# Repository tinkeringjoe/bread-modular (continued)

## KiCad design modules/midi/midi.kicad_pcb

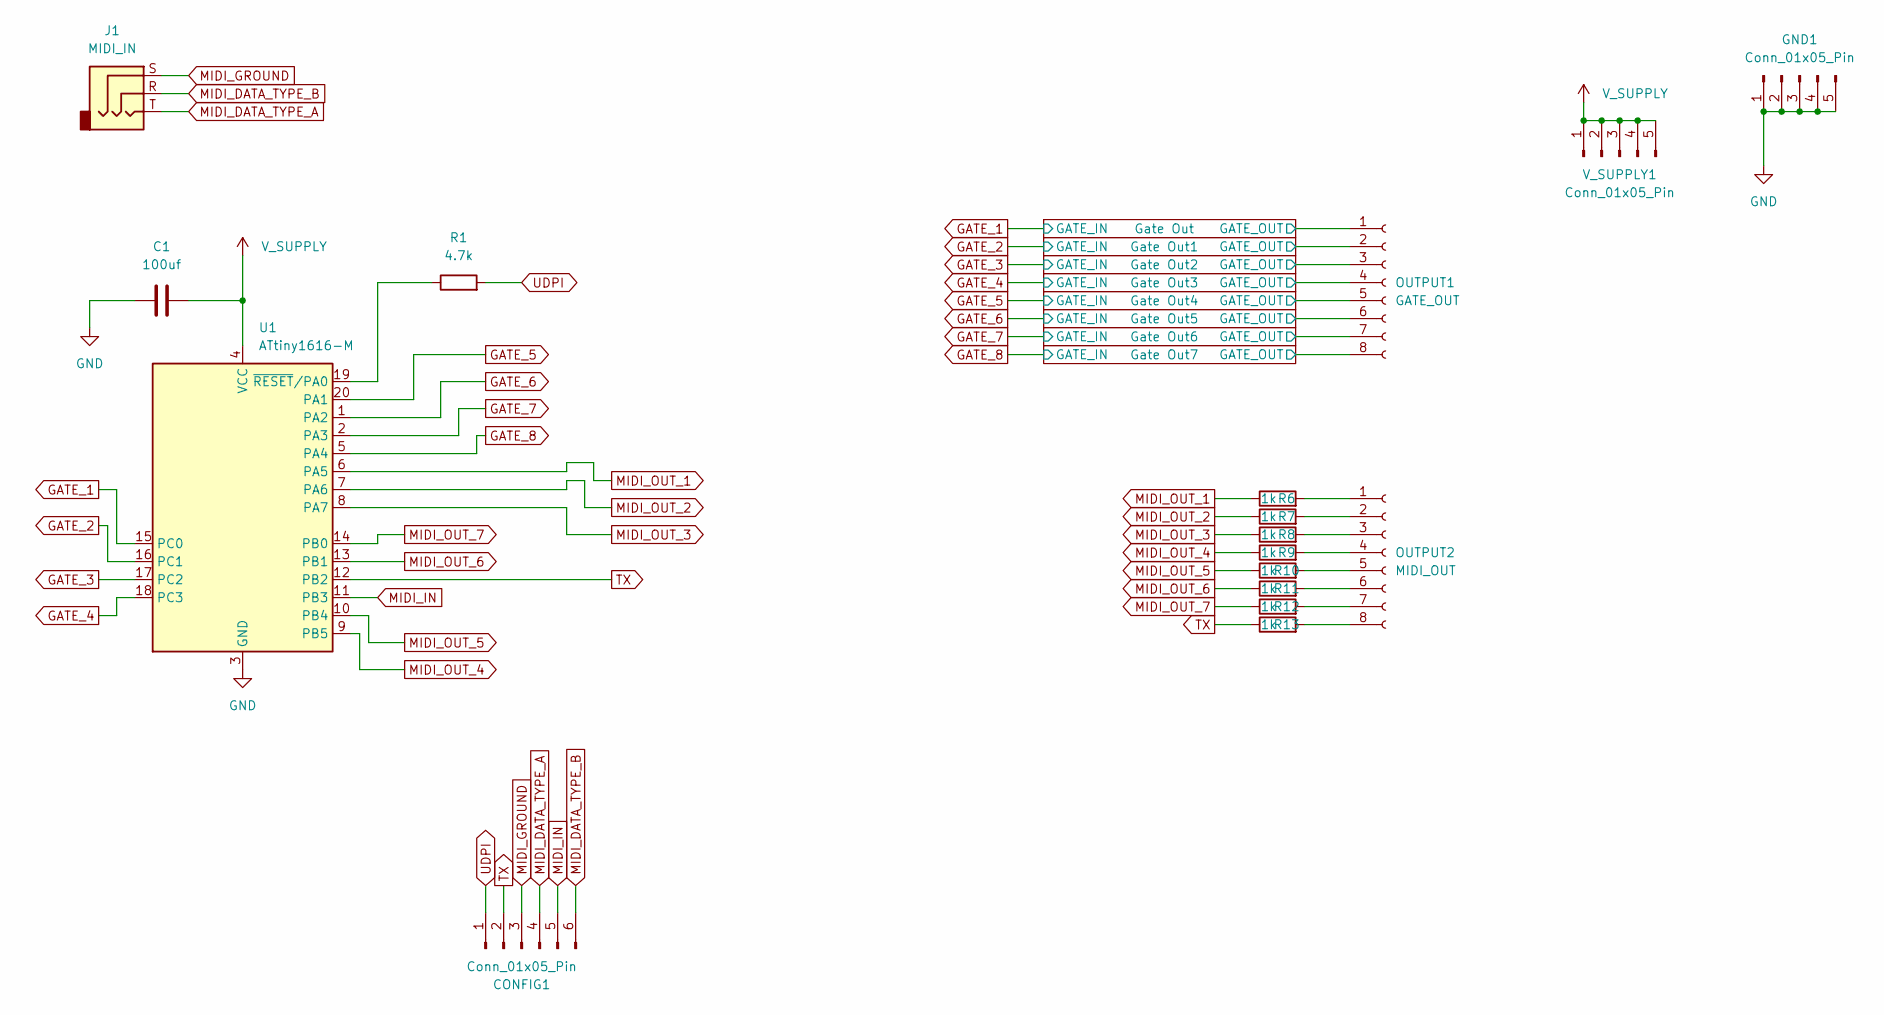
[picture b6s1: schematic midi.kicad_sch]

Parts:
C1: 100uf; C_1206_3216Metric
CONFIG1: Conn_01x05_Pin; Conn_Holes_6
GND1: Conn_01x05_Pin; Power_Connector
J1: MIDI_IN; Jack_3.5mm_QingPu_WQP-PJ366ST_Vertical
OUTPUT1: GATE_OUT; PinSocket_1x08_P2.54mm_Vertical
OUTPUT2: MIDI_OUT; PinSocket_1x08_P2.54mm_Vertical
R1: 4.7k; R_0402_1005Metric
R6, R7, R8, R9, R10, R11, R12, R13: 1k; R_0402_1005Metric
U1: ATtiny1616-M; VQFN-20-1EP_3x3mm_P0.4mm_EP1.7x1.7mm
V_SUPPLY1: Conn_01x05_Pin; Power_Connector

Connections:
/Gate Out1/GATE_OUT: OUTPUT1.2; also elsewhere on the board
/Gate Out2/GATE_OUT: OUTPUT1.3; also elsewhere on the board
/Gate Out3/GATE_OUT: OUTPUT1.4; also elsewhere on the board
/Gate Out4/GATE_OUT: OUTPUT1.5; also elsewhere on the board
/Gate Out5/GATE_OUT: OUTPUT1.6; also elsewhere on the board
/Gate Out6/GATE_OUT: OUTPUT1.7; also elsewhere on the board
/Gate Out7/GATE_OUT: OUTPUT1.8; also elsewhere on the board
/Gate Out/GATE_OUT: OUTPUT1.1; also elsewhere on the board
GATE_1: U1.15 (PC0); also elsewhere on the board
GATE_2: U1.16 (PC1); also elsewhere on the board
GATE_3: U1.17 (PC2); also elsewhere on the board
GATE_4: U1.18 (PC3); also elsewhere on the board
GATE_5: U1.20 (PA1); also elsewhere on the board
GATE_6: U1.1 (PA2); also elsewhere on the board
GATE_7: U1.2 (PA3); also elsewhere on the board
GATE_8: U1.5 (PA4); also elsewhere on the board
GND: C1.1, GND1.1, GND1.2, GND1.3, GND1.4, GND1.5, U1.3 (GND), U1.21 (GND); also elsewhere on the board
MIDI_DATA_TYPE_A: CONFIG1.4, J1.T
MIDI_DATA_TYPE_B: CONFIG1.6, J1.R
MIDI_GROUND: CONFIG1.3, J1.S
MIDI_IN: CONFIG1.5, U1.11 (PB3)
MIDI_OUT_1: R6.1, U1.6 (PA5)
MIDI_OUT_2: R7.1, U1.7 (PA6)
MIDI_OUT_3: R8.1, U1.8 (PA7)
MIDI_OUT_4: R9.1, U1.9 (PB5)
MIDI_OUT_5: R10.1, U1.10 (PB4)
MIDI_OUT_6: R11.1, U1.13 (PB1)
MIDI_OUT_7: R12.1, U1.14 (PB0)
unnamed: OUTPUT2.1, R6.2
unnamed: OUTPUT2.2, R7.2
unnamed: OUTPUT2.3, R8.2
unnamed: OUTPUT2.4, R9.2
unnamed: OUTPUT2.5, R10.2
unnamed: OUTPUT2.6, R11.2
unnamed: OUTPUT2.7, R12.2
unnamed: OUTPUT2.8, R13.2
unnamed: R1.1, U1.19 (~RESET/PA0)
TX: CONFIG1.2, R13.1, U1.12 (PB2)
UDPI: CONFIG1.1, R1.2
V_SUPPLY: C1.2, U1.4 (VCC), V_SUPPLY1.1, V_SUPPLY1.2, V_SUPPLY1.3, V_SUPPLY1.4, V_SUPPLY1.5; also elsewhere on the board

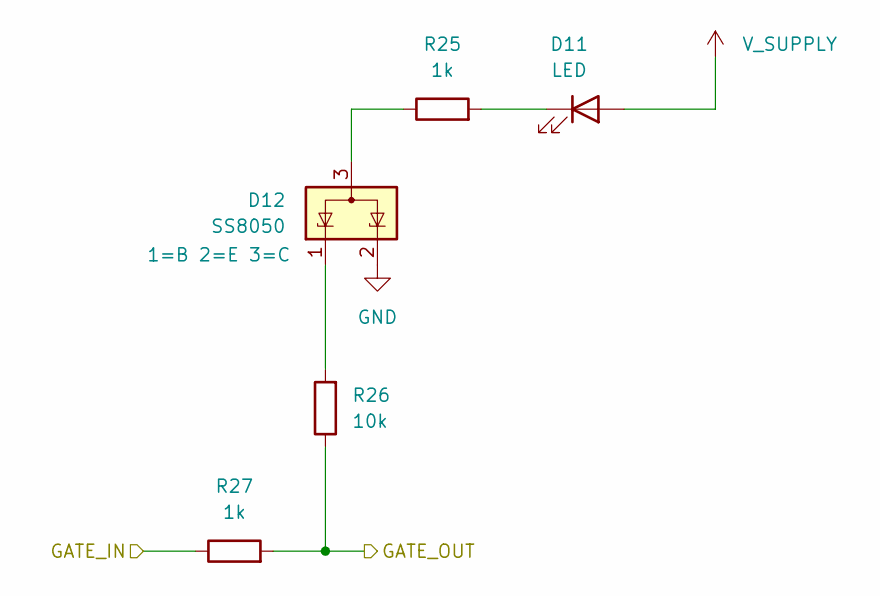
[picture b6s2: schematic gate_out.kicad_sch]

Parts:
D11: LED; LED_0603_1608Metric
D12: SS8050; SOT-23
R25, R27: 1k; R_0402_1005Metric
R26: 10k; R_0402_1005Metric

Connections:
/Gate Out5/GATE_OUT: R26.1, R27.2; also elsewhere on the board
GATE_6: R27.1; also elsewhere on the board
GND: D12.2 (K); also elsewhere on the board
unnamed: D11.1 (K), R25.2
unnamed: D12.3 (A), R25.1
unnamed: D12.1 (K), R26.2
V_SUPPLY: D11.2 (A); also elsewhere on the board

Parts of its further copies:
D1, D4, D6, D8, D13, D15, D100: LED; LED_0603_1608Metric
D2, D3, D5, D7, D10, D14, D16: SS8050; SOT-23
R2, R4, R14, R15, R17, R19, R21, R22, R24, R28, R30, R31, R33, R44: 1k; R_0402_1005Metric
R3, R5, R16, R20, R23, R29, R32: 10k; R_0402_1005Metric

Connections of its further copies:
/Gate Out1/GATE_OUT: R3.1, R14.2; also elsewhere on the board
/Gate Out2/GATE_OUT: R16.1, R17.2; also elsewhere on the board
/Gate Out3/GATE_OUT: R20.1, R21.2; also elsewhere on the board
/Gate Out4/GATE_OUT: R23.1, R24.2; also elsewhere on the board
/Gate Out6/GATE_OUT: R29.1, R30.2; also elsewhere on the board
/Gate Out7/GATE_OUT: R32.1, R33.2; also elsewhere on the board
/Gate Out/GATE_OUT: R5.1, R44.2; also elsewhere on the board
GATE_1: R44.1; also elsewhere on the board
GATE_2: R14.1; also elsewhere on the board
GATE_3: R17.1; also elsewhere on the board
GATE_4: R21.1; also elsewhere on the board
GATE_5: R24.1; also elsewhere on the board
GATE_7: R30.1; also elsewhere on the board
GATE_8: R33.1; also elsewhere on the board
GND: D2.2 (K), D3.2 (K), D5.2 (K), D7.2 (K), D10.2 (K), D14.2 (K), D16.2 (K); also elsewhere on the board
unnamed: D1.1 (K), R2.2
unnamed: D2.3 (A), R4.1
unnamed: D2.1 (K), R5.2
unnamed: D3.3 (A), R2.1
unnamed: D3.1 (K), R3.2
unnamed: D4.1 (K), R15.2
unnamed: D5.3 (A), R15.1
unnamed: D5.1 (K), R16.2
unnamed: D6.1 (K), R19.2
unnamed: D7.3 (A), R19.1
unnamed: D7.1 (K), R20.2
unnamed: D8.1 (K), R22.2
unnamed: D10.3 (A), R22.1
unnamed: D10.1 (K), R23.2
unnamed: D13.1 (K), R28.2
unnamed: D14.3 (A), R28.1
unnamed: D14.1 (K), R29.2
unnamed: D15.1 (K), R31.2
unnamed: D16.3 (A), R31.1
unnamed: D16.1 (K), R32.2
unnamed: D100.1 (K), R4.2
V_SUPPLY: D1.2 (A), D4.2 (A), D6.2 (A), D8.2 (A), D13.2 (A), D15.2 (A), D100.2 (A); also elsewhere on the board

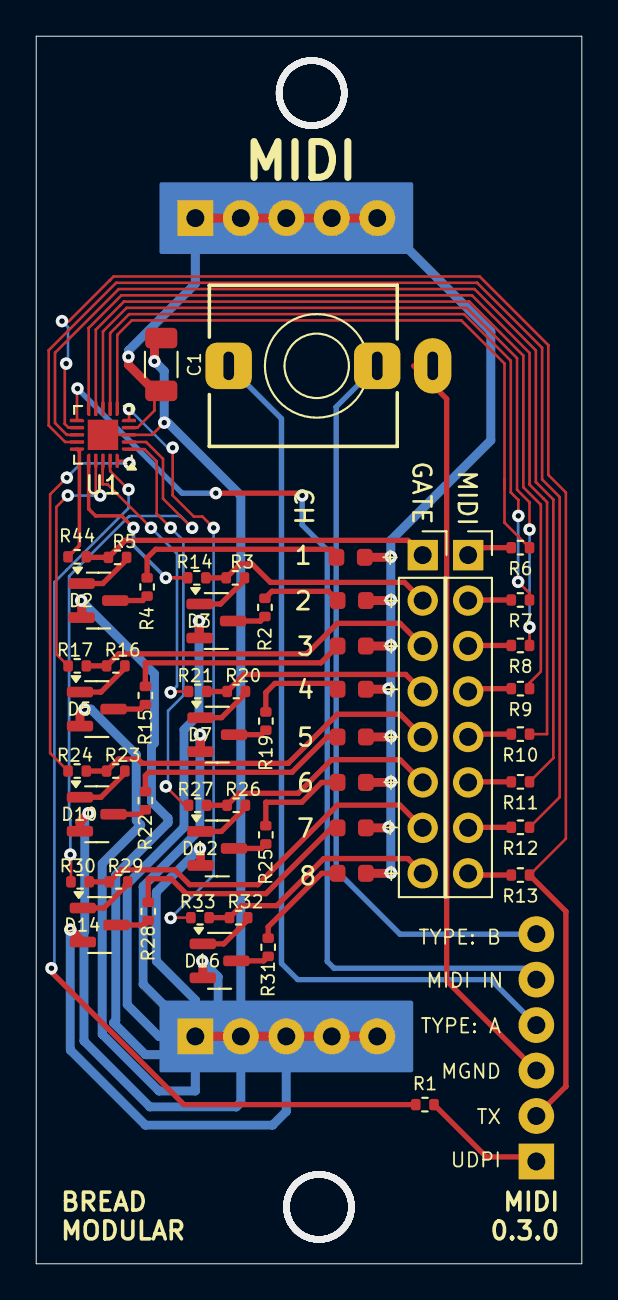
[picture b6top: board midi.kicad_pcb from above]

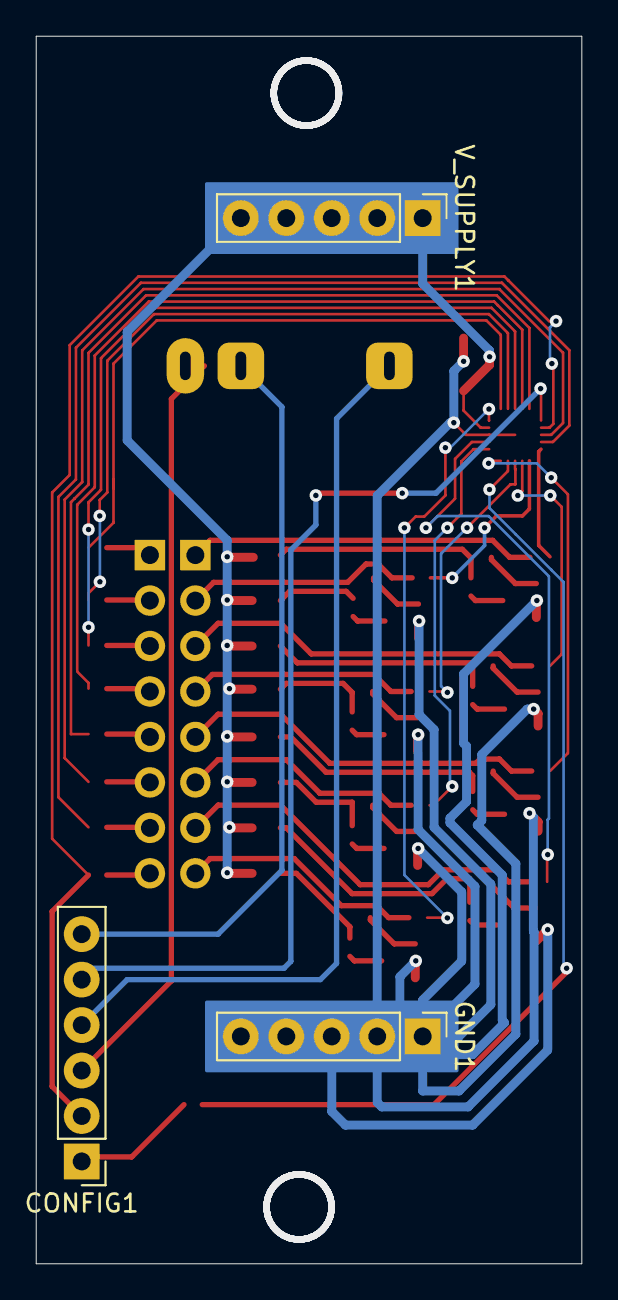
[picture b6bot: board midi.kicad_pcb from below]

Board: 2 copper layers, 30.5 x 68.6 mm, 57 parts (3 on the bottom side), 64 nets.

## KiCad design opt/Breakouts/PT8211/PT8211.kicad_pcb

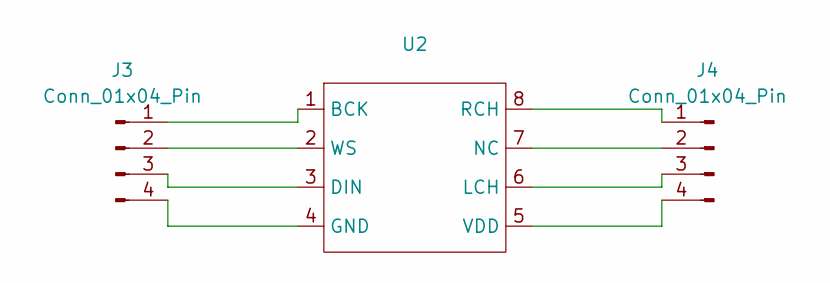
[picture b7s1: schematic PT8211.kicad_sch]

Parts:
J3, J4: Conn_01x04_Pin; PinSocket_1x04_P2.54mm_Vertical
U2: SOIC-8-1EP_3.9x4.9mm_P1.27mm_EP2.29x3mm

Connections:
unnamed: J3.1, U2.1 (BCK)
unnamed: J3.2, U2.2 (WS)
unnamed: J3.3, U2.3 (DIN)
unnamed: J3.4, U2.4 (GND)
unnamed: J4.1, U2.8 (RCH)
unnamed: J4.2, U2.7 (NC)
unnamed: J4.3, U2.6 (LCH)
unnamed: J4.4, U2.5 (VDD)

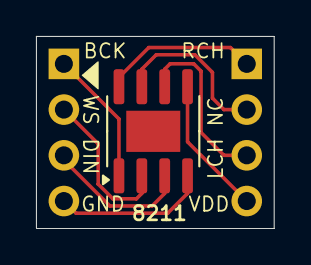
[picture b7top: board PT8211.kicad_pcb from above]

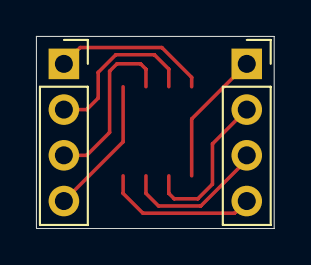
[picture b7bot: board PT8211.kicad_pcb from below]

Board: 2 copper layers, 13.2 x 10.7 mm, 3 parts (2 on the bottom side), 8 nets.

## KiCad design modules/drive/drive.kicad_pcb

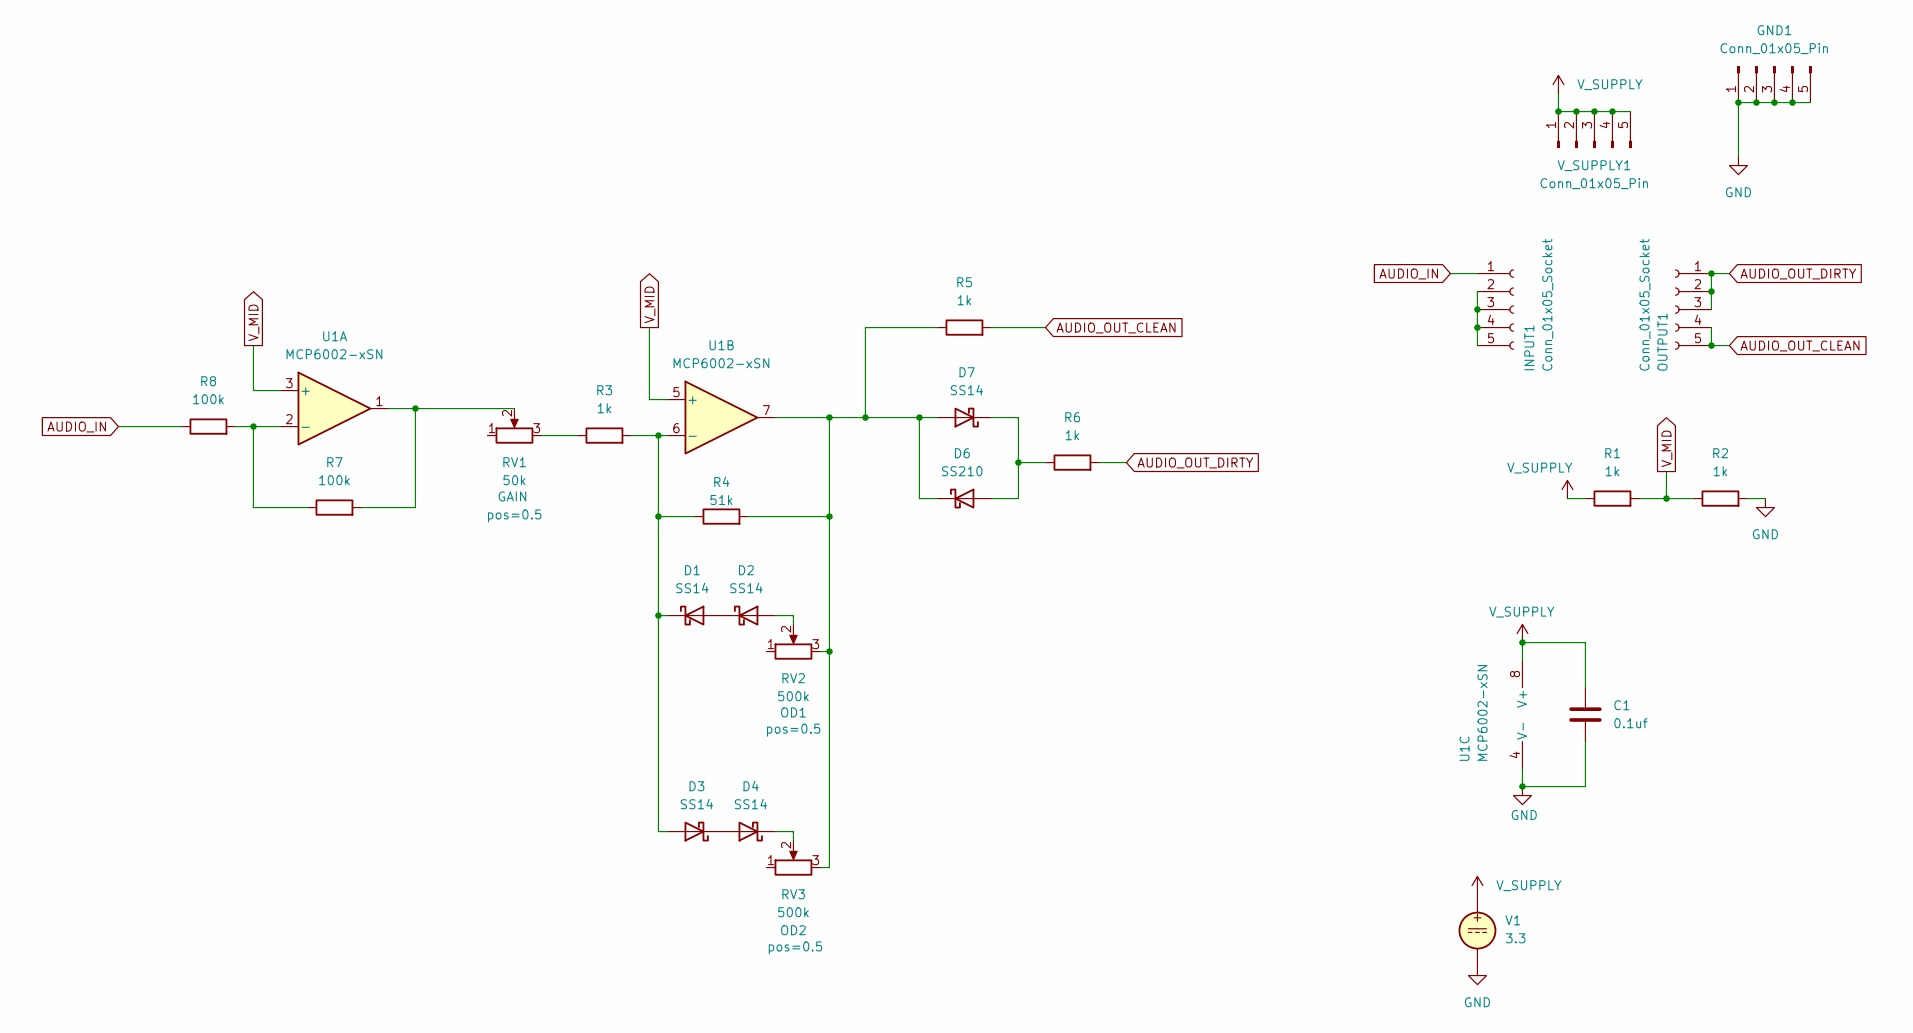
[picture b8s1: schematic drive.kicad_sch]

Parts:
C1: 0.1uf; C_0402_1005Metric
D1, D2, D3, D4, D7: SS14; D_SMA
D6: SS210; D_SMA
GND1: Conn_01x05_Pin; Power_Connector
INPUT1: Conn_01x05_Socket; PinSocket_1x05_P2.54mm_Vertical
OUTPUT1: Conn_01x05_Socket; PinSocket_1x05_P2.54mm_Vertical
R1, R2, R3, R5, R6: 1k; R_0402_1005Metric
R4: 51k; R_0402_1005Metric
R7, R8: 100k; R_0402_1005Metric
RV1: 50k; Potentiometer_RV09
RV2, RV3: 500k; Potentiometer_RV09
U1: MCP6002-xSN; SOIC-8-1EP_3.9x4.9mm_P1.27mm_EP2.29x3mm
V1: 3.3
V_SUPPLY1: Conn_01x05_Pin; Power_Connector

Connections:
AUDIO_IN: INPUT1.1, R8.1
AUDIO_OUT_CLEAN: OUTPUT1.4, OUTPUT1.5, R5.2
AUDIO_OUT_DIRTY: OUTPUT1.1, OUTPUT1.2, OUTPUT1.3, R6.2
GND: C1.2, GND1.1, GND1.2, GND1.3, GND1.4, GND1.5, R2.2, U1.4 (V-), V1.2
unnamed: D1.2 (A), D2.1 (K)
unnamed: D1.1 (K), D3.2 (A), R3.2, R4.1, U1.6 (-)
unnamed: D2.2 (A), RV2.2
unnamed: D3.1 (K), D4.2 (A)
unnamed: D4.1 (K), RV3.2
unnamed: D6.2 (A), D7.1 (K), R6.1
unnamed: D6.1 (K), D7.2 (A), R4.2, R5.1, RV2.3, RV3.3, U1.7
unnamed: INPUT1.2, INPUT1.3, INPUT1.4, INPUT1.5
unnamed: R3.1, RV1.3
unnamed: R7.2, RV1.2, U1.1
unnamed: R7.1, R8.2, U1.2 (-)
V_MID: R1.2, R2.1, U1.3 (+), U1.5 (+)
V_SUPPLY: C1.1, R1.1, U1.8 (V+), V1.1, V_SUPPLY1.1, V_SUPPLY1.2, V_SUPPLY1.3, V_SUPPLY1.4, V_SUPPLY1.5

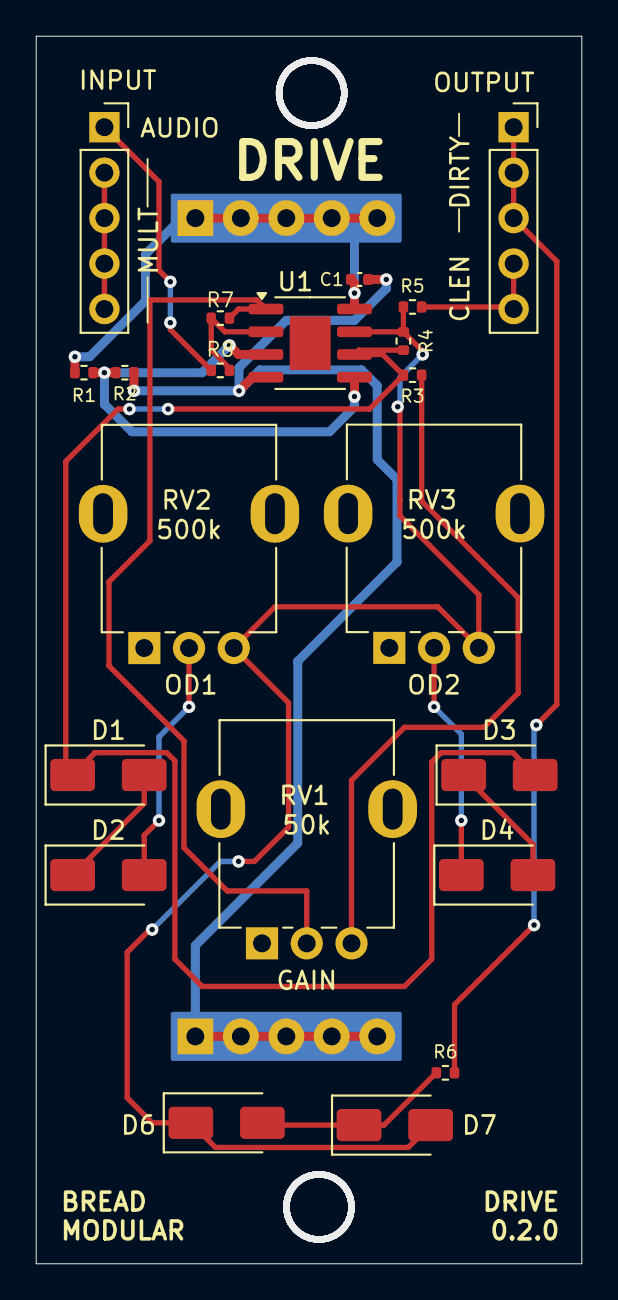
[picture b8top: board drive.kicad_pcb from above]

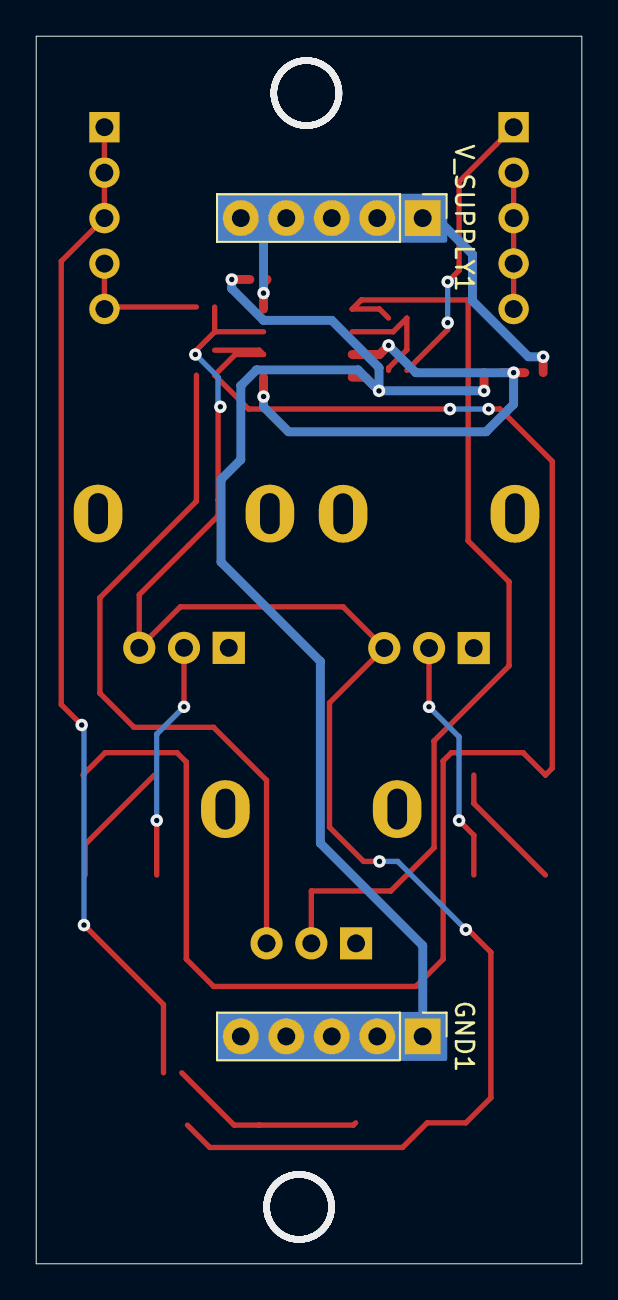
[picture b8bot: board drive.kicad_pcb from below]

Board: 2 copper layers, 30.5 x 68.6 mm, 23 parts (2 on the bottom side), 17 nets.

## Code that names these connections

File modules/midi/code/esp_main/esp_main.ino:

/* Arduino ATTiny 1616 Pin Map

  0 - PA4
  1 - PA5
  2 - PA6
  3 - PA7
  4 - PB5
  5 - PB4
  6 - PB3, RX
  7 - PB2, TX
  8 - PB1
  9 - PB0
  10 - PC0
  11 - PC1
  12 - PC2
  13 - PC3
  14 - PA1
  15 - PA2
  16 - PA3
*/

#include <MIDI.h>
#include <SoftwareSerial.h>

// Create a MIDI object
MIDI_CREATE_INSTANCE(HardwareSerial, Serial, MIDI);

#define PIN_RX 6 // PB3
#define PIN_TX 7 // PB2

// Define the Gate Pins
#define GATE_PIN_01 10 // PC0
#define GATE_PIN_02 11 // PC1
#define GATE_PIN_03 12 // PC2
#define GATE_PIN_04 13 // PC3
#define GATE_PIN_05 14 // PA1
#define GATE_PIN_06 15 // PA2
#define GATE_PIN_07 16 // PA3
#define GATE_PIN_08 0 // PA4

// Define IMIDI Pins
#define IMIDI_PIN_01 1 // PA5
#define IMIDI_PIN_02 2 // PA6
#define IMIDI_PIN_03 3 // PA7
#define IMIDI_PIN_04 4 // PB5
#define IMIDI_PIN_05 5 // PB4
#define IMIDI_PIN_06 8 // PB1
#define IMIDI_PIN_07 9 // PB0

SoftwareSerial midiSerialArray[] = {
    SoftwareSerial(-1, IMIDI_PIN_01),
    SoftwareSerial(-1, IMIDI_PIN_02),
    SoftwareSerial(-1, IMIDI_PIN_03),
    SoftwareSerial(-1, IMIDI_PIN_04),
    SoftwareSerial(-1, IMIDI_PIN_05),
    SoftwareSerial(-1, IMIDI_PIN_06),
    SoftwareSerial(-1, IMIDI_PIN_07),
};

int getGatePin(int id) {
  switch (id) {
    case 1:
      return GATE_PIN_01;
    case 2:
      return GATE_PIN_02;
    case 3:
      return GATE_PIN_03;
    case 4:
      return GATE_PIN_04;
    case 5:
      return GATE_PIN_05;
    case 6:
      return GATE_PIN_06;
    case 7:
      return GATE_PIN_07;
    case 8:
      return GATE_PIN_08;
    default:
      return -1;
  }
}

void setupGates() {
  for (int x = 1; x <= 8; x = x + 1) {
    int gatePin = getGatePin(x);
    pinMode(gatePin, OUTPUT);
    digitalWrite(gatePin, LOW);
  }
}

void setupIMIDI() {
  pinMode(IMIDI_PIN_01, OUTPUT);
  pinMode(IMIDI_PIN_02, OUTPUT);
  pinMode(IMIDI_PIN_03, OUTPUT);
  pinMode(IMIDI_PIN_04, OUTPUT);
  pinMode(IMIDI_PIN_05, OUTPUT);
  pinMode(IMIDI_PIN_06, OUTPUT);
  pinMode(IMIDI_PIN_07, OUTPUT);

  for (int i = 0; i < 7; i++) {
    midiSerialArray[i].begin(31250); // Start each SoftwareSerial at MIDI baud rate
  }
}

void handleNoteOn(byte channel, byte note, byte velocity) {
  int gatePin = getGatePin(channel);
  if (gatePin != -1) {
    digitalWrite(gatePin, HIGH);
  }
  
  sendMIDI(channel, 0x90, note, velocity);
}

// Callback for Note Off messages
void handleNoteOff(byte channel, byte note, byte velocity) {
  int gatePin = getGatePin(channel);
  if (gatePin != -1) {
    digitalWrite(gatePin, LOW);
  }

  sendMIDI(channel, 0x80, note, velocity);
}

void sendMIDI(byte channel, byte status, byte data1, byte data2) {
  int channelIndex = channel - 1;
  if (channelIndex >= 0 && channelIndex < 7) {
    SoftwareSerial serialCh = midiSerialArray[channelIndex];
    serialCh.write(status); // Send the status byte
    serialCh.write(data1);  // Send the first data byte
    serialCh.write(data2);  // Send the second data byte
  }
}

void setup() {
  setupGates();

  Serial.begin(31250);
   // Initialize the MIDI library
  MIDI.begin(MIDI_CHANNEL_OMNI); // Listen to all MIDI channels
  MIDI.setHandleNoteOn(handleNoteOn);
  MIDI.setHandleNoteOff(handleNoteOff);

  setupIMIDI();

  Serial.println("MIDI Listening Started!");
}

void loop() {
  MIDI.read();
}

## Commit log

2024-10-04 Create LICENSE
2024-10-04 Add the 4_ATT module
2024-10-04 Add aa module for the buff_mix
2024-10-04 Add the final buff_mix
2024-10-07 Add line_in schematic
2024-10-07 Add the schematic for the PCB
2024-10-07 Update the line-in module
2024-10-07 Make sure SMD via are not placed on pads.
2024-10-07 version line_in_0.2.0
2024-10-14 Retouched the Blank Module with new sizes.
2024-10-14 Add the gitignore file
2024-10-14 Add basic version of 4_mix
2024-10-14 Implement the simulation model.
2024-10-15 Updated the core design
2024-10-15 Fixed some pcb layout issues.
2024-10-15 Add the full mixer
2024-10-16 Schematics is done. Now it's time for PCB layout.
2024-10-16 Add some external KiCad footprints lib.
2024-10-16 Implemented the PCB design of 4_mix
2024-10-16 Change some routing rules.
2024-10-16 Finalized 4_mix for production
2024-10-16 Add sockets for the blank project.
2024-10-17 Start working on the new version of line_in
2024-10-17 Finalize the core design
2024-10-17 Add AudioJacks submodule with KiCad footprints.
2024-10-17 Finalize the schematic design
2024-10-17 Finished building the line_in module.
2024-10-17 Add the line_in 0.3.0 production build
2024-10-18 Add the initial version of the line_out
2024-10-18 Finalized the line_out module.
2024-10-20 Build line_out for production
2024-10-20 Add BreakoutBoards for popular opamps.
2024-10-20 Finlalized schematic for head_out module.
2024-10-20 Finished pcb_design of the head_out
2024-10-20 Finialize the design based on actual wattage requirements.
2024-10-21 Finalize the head_out module.
2024-10-27 Use TL072 the current version has some pops and cracks LM358 could be the issue. So, we are trying TL072
2024-10-27 4_mix_0.2.0
2024-10-27 Use MCP6002 in the 4_mix. This provides more headroom due to it's rail-2-rail output.
2024-10-27 4_mix_0.3.0
2024-10-28 Add missing production files for 4_mix
2024-10-28 4_mix_0.3.1
2024-10-28 Update the basic kidcad app Add simulation support Introduce the version number silkscreen
2024-10-28 Setup JVCA
2024-10-28 Implement the basic setup. CV support is not done and there are no CV control implemented.
2024-10-28 Finish the jvca signal handling.
2024-10-28 Add CV controlling support
2024-10-29 Assigned footprints
2024-10-29 Implemented JVCA PCB
2024-10-29 Fix the simulation a bit.
2024-10-29 Add jvca production data
2024-10-29 jcva_0.1.0
2024-11-01 Implement the base
2024-11-01 Add the version text
2024-11-01 base_1.0.0
2024-11-01 Created a RV_09 base Now we can use these inside the breadboard along with some circuit. Or inside BBM Base.
2024-11-01 rv_base_0.1.0
2024-11-03 Update the blank module with more details.
2024-11-03 Finished the schematic
2024-11-04 Finalize the PCB
2024-11-04 ar_env_0.1.0
2024-11-04 Changed the 6.8k resistor package. Used 0603 package due to availability in JLCPCB
2024-11-04 ar_env_0.1.1
2024-11-05 Finished schematic of wave module.
2024-11-05 Finish schematics
2024-11-05 Initiate the PCB layut
2024-11-05 Finished PCB design.
2024-11-05 wave_0.1.0
2024-11-05 Add README for the wave project.
2024-11-05 Add output wave captions.
2024-11-05 wave_0.1.1
2024-11-06 Introduce a README for JVCA
2024-11-06 Add the initial version
2024-11-06 usb_power_0.1.0
2024-11-06 Changed the orientation of the USB C port
2024-11-06 usb_power_0.1.1
2024-11-06 Add usb_power Readme
2024-11-06 Update TypeC.pretty to use our own fork with changes.
2024-11-07 Change usb_power for the TypeC footprint update.
2024-11-07 usb_power_0.1.2
2024-11-08 Implement 5V DC Power setup.
2024-11-08 dc_power_0.1.0
2024-11-10 Add power/gnd jacks
2024-11-10 base_0.2.0
2024-11-10 Add 2 jack sockets for cascading support.
2024-11-10 base_0.2.1
2024-11-12 Add the schematic of low_pass filter
2024-11-12 Add Sallen Key capacitors with commonly available caps
2024-11-12 Making the schematic ready for PCB
2024-11-12 Finalized the design
2024-11-12 layout components in the PCB
2024-11-12 update pcb layout
2024-11-13 Finalized the PCB design
2024-11-13 Build production files of low_pass
2024-11-13 Finalized low_pass
2024-11-13 low_pass_0.1.0
2024-11-14 Finished the schematic for v2ca
2024-11-14 Finished the PCB layout.
2024-11-14 Add the production version.
2024-11-14 v2ca_0.1.0
2024-11-14 Add AR_ENV README.
2024-11-15 Designed the new buff_mix 0.2.0 schematic.
2024-11-15 Add the PCB layout of buff_mix
2024-11-15 Finished routing and production build
2024-11-16 buff_mix_0.2.0
2024-11-17 Add production files.
2024-11-17 usb_power_0.2.0
2024-11-17 Update line_in to use MCP6001 and 3V3.
2024-11-17 Add production line_in 0.2.0
2024-11-17 line_in_0.2.0
2024-11-17 line_in_0.4.0
2024-11-17 Update the blank module.
2024-11-18 Add the basic schematic.
2024-11-18 Add MIDI PCB
2024-11-18 Finalized the midi module.
2024-11-20 Add Attiny1616 board
2024-11-20 midi_0.1.0
2024-11-21 Finalized Kick schamatic
2024-11-22 Assign footprints and PCB ready.
2024-11-22 Finished the 4 layer board.
2024-11-22 kick_0.1.0
2024-11-23 Introduced new low_pass gate.
2024-11-24 Finalized the schematic of low_pass
2024-11-24 low_pass_0.2.0
2024-11-24 Removed the usb_power tactile switch
2024-11-24 usb_power_0.3.0
2024-11-25 Add the dummy code
2024-11-26 Implement the MIDI to Gate setup with ATTiny1616
2024-11-26 Add POC support for modular MIDI
2024-11-26 Add iMIDI support to the midi
2024-11-27 Implement the PCB layout and routing
2024-11-27 Add production files
2024-11-27 midi_0.2.0
2024-11-30 Add 1616 Tone codes.
2024-11-30 Add MIDI and gate support
2024-12-02 Add support for detuning.
2024-12-04 Send the velocity out via PA6
2024-12-05 Add schematics for the mco
2024-12-05 Finalized the PCB design of MCO
2024-12-05 Add production files for mco
2024-12-05 mco_0.1.0
2024-12-05 Convert midi codebase into platformio
2024-12-06 Removed old arduino midi codebase
2024-12-06 midi_0.2.1
2024-12-07 Add basic noise setup
2024-12-07 Implement noise tone control
2024-12-08 Implement the noise schematics
2024-12-09 Implement the PCB routing
2024-12-09 Add noise_0.1.0 production files.
2024-12-09 noise_0.1.0
2024-12-09 increased the overall delay time of the noise module code
2024-12-09 noise_0.1.1
2024-12-10 Implement the basic SVF simulation.
2024-12-11 Implement the base filter simulation
2024-12-11 Implement the final schematic for SVF
2024-12-11 Add inline documentation for the SVF
2024-12-11 Simplify the SVF design with just freq & resonance knobs
2024-12-11 Getting it ready for PCB routing
2024-12-12 Finalized the PCB routing
2024-12-12 Change the opt Kicad lib repository.
2024-12-12 svf_0.1.0
2024-12-13 Add CVMath codebase
2024-12-13 Make sure cv calculations are normalized
2024-12-14 Add a basic mode select setup
2024-12-14 Write the mode to the EEPROM
2024-12-14 Add codebase for all the modes
2024-12-14 Introduce the schematic
2024-12-14 Implement the schematic of cv_math
2024-12-15 Finished cv_math PCB routing
2024-12-15 Add cv_math production files
2024-12-15 cv_math_0.1.0
2024-12-15 Implement a basic xpand algorithm for cv_math
2024-12-15 cv_math_0.1.1
2024-12-15 cv_math: xpand now uses distance to scale this will make the waveform strech to the highest. It's bottom part won't move anywhere
2024-12-15 cv_math_0.1.2
2024-12-16 drive: Implement the schematics
2024-12-16 drive: finished pcb routing
2024-12-16 drive: add production files
2024-12-16 drive_0.1.0
2024-12-21 blank:Add opamp & pot as a built-in components These are used in almost all the projects. So, having pre-build components make is easy to get started
2024-12-21 started with the filter and VCA
2024-12-21 Implement the gate to pulse generator.
2024-12-21 Add a opamp buffer for the CV_ACCENT
2024-12-22 Finished schematics
2024-12-23 Started basic pcb layout
2024-12-23 Complete CPU routing
2024-12-23 hihat_0.1.0
2024-12-23 Add schematic for i_mix
2024-12-24 i_mix_0.1.0
2024-12-24 svf: make it louder & add curve control Now the SVF is 8db louder in general. Now the resonance control active troughout the potentiometer Add the curve support for the freq so, we can target low or 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
2024-12-24 svf_0.2.0
2024-12-24 svf: add production files for 0.2.0
2024-12-24 svf_0.2.1
2024-12-24 Add the base skeliton
2024-12-24 Introduce a timer based DAC output setup
2024-12-24 Introduce wavetable generator
2024-12-24 Use 2048 samples
2024-12-25 Triangle wave oscillators
2024-12-25 Add support for detuning
2024-12-25 Add unison and CV support
2024-12-26 Add mode selector for 3 types of waves: 1. sine 2. tri 3. square
2024-12-26 Add mco_0.2.0 schematic
2024-12-27 mco_0.2.0
2024-12-27 drive: Remove radio freq. capturing with the gain. This is due to the high-gain nature & the use of non-inverting buffer. Now change it to an inverting buffer & all is gone.
2024-12-27 drive_0.2.0
2024-12-31 Add the basic kick sampler
2024-12-31 base: Add USB power setup to the base
2024-12-31 base_0.3.0
2025-01-01 breakouts: Add ESP32-S3-MINI-1
2025-01-01 breakout: Add PT8211 breakout
2025-01-02 base: update the usb-c socket for proper copper layers
2025-01-02 base_0.3.1
2025-01-02 breakouts: Merge ESP32 and PT8211 pcbs
2025-01-02 Introduce some key samples
2025-01-04 gate_0.1.0
2025-01-07 Add support to play samples via MIDI input
2025-01-07 Add a simple perc player which sounds quite good.
2025-01-07 Add 8-note polyphony support
2025-01-08 Add more samples
2025-01-08 Add Velocity support
2025-01-08 mco_0.3.0
2025-01-08 midi: Add support to select MIDI A or B
2025-01-08 midi_0.3.0
2025-01-08 hihat: Add MIDI support Now we don't need seperate cables for GATE, Accent & Open Hat. We can control all these via a single MIDI cable.
2025-01-08 hihat_0.2.0
2025-01-10 8bit: Introduce 8bit This is just the same as the current version of MCO. It's an Attiny 1616 powered chip with 8-bit audio output.
2025-01-10 8bit_0.1.0
2025-01-10 mco: Rebrand the 0.1.0 version as the new MCO. We removed CV support and it's not needed.
2025-01-10 mco_0.4.0
2025-01-15 i_mix: Use inverting buffers This will reducing picking up noise coming from cables
2025-01-15 imix: change naming from i_mix to imix
2025-01-15 Move deprecated modules into it's own directory
2025-01-15 imix_0.2.0
2025-01-15 modules: rename deprecated to _deprecated
2025-01-15 rename low_pass to low
2025-01-15 base: Remove power extention via TRS cable Even with the regulator, it's noisy. So, instead now we use TRS only for syncing the ground between boards
2025-01-15 base_0.4.0
2025-01-15 midi: Update firmware to route MIDI CC Along with this, we use our SimpleMIDI library for clarity.
2025-01-15 midi_0.3.1
2025-01-17 Change uc to SOIC
    Changing the packaging of the micro to SOIC for easier hand soldering.
